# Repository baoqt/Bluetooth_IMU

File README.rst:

================= =====
Supported Targets ESP32
================= =====

BT_IMU_2_0
======================

Firmware and PCB design of an IMU sensor board to be used with stroke rehabilitation and data collection.

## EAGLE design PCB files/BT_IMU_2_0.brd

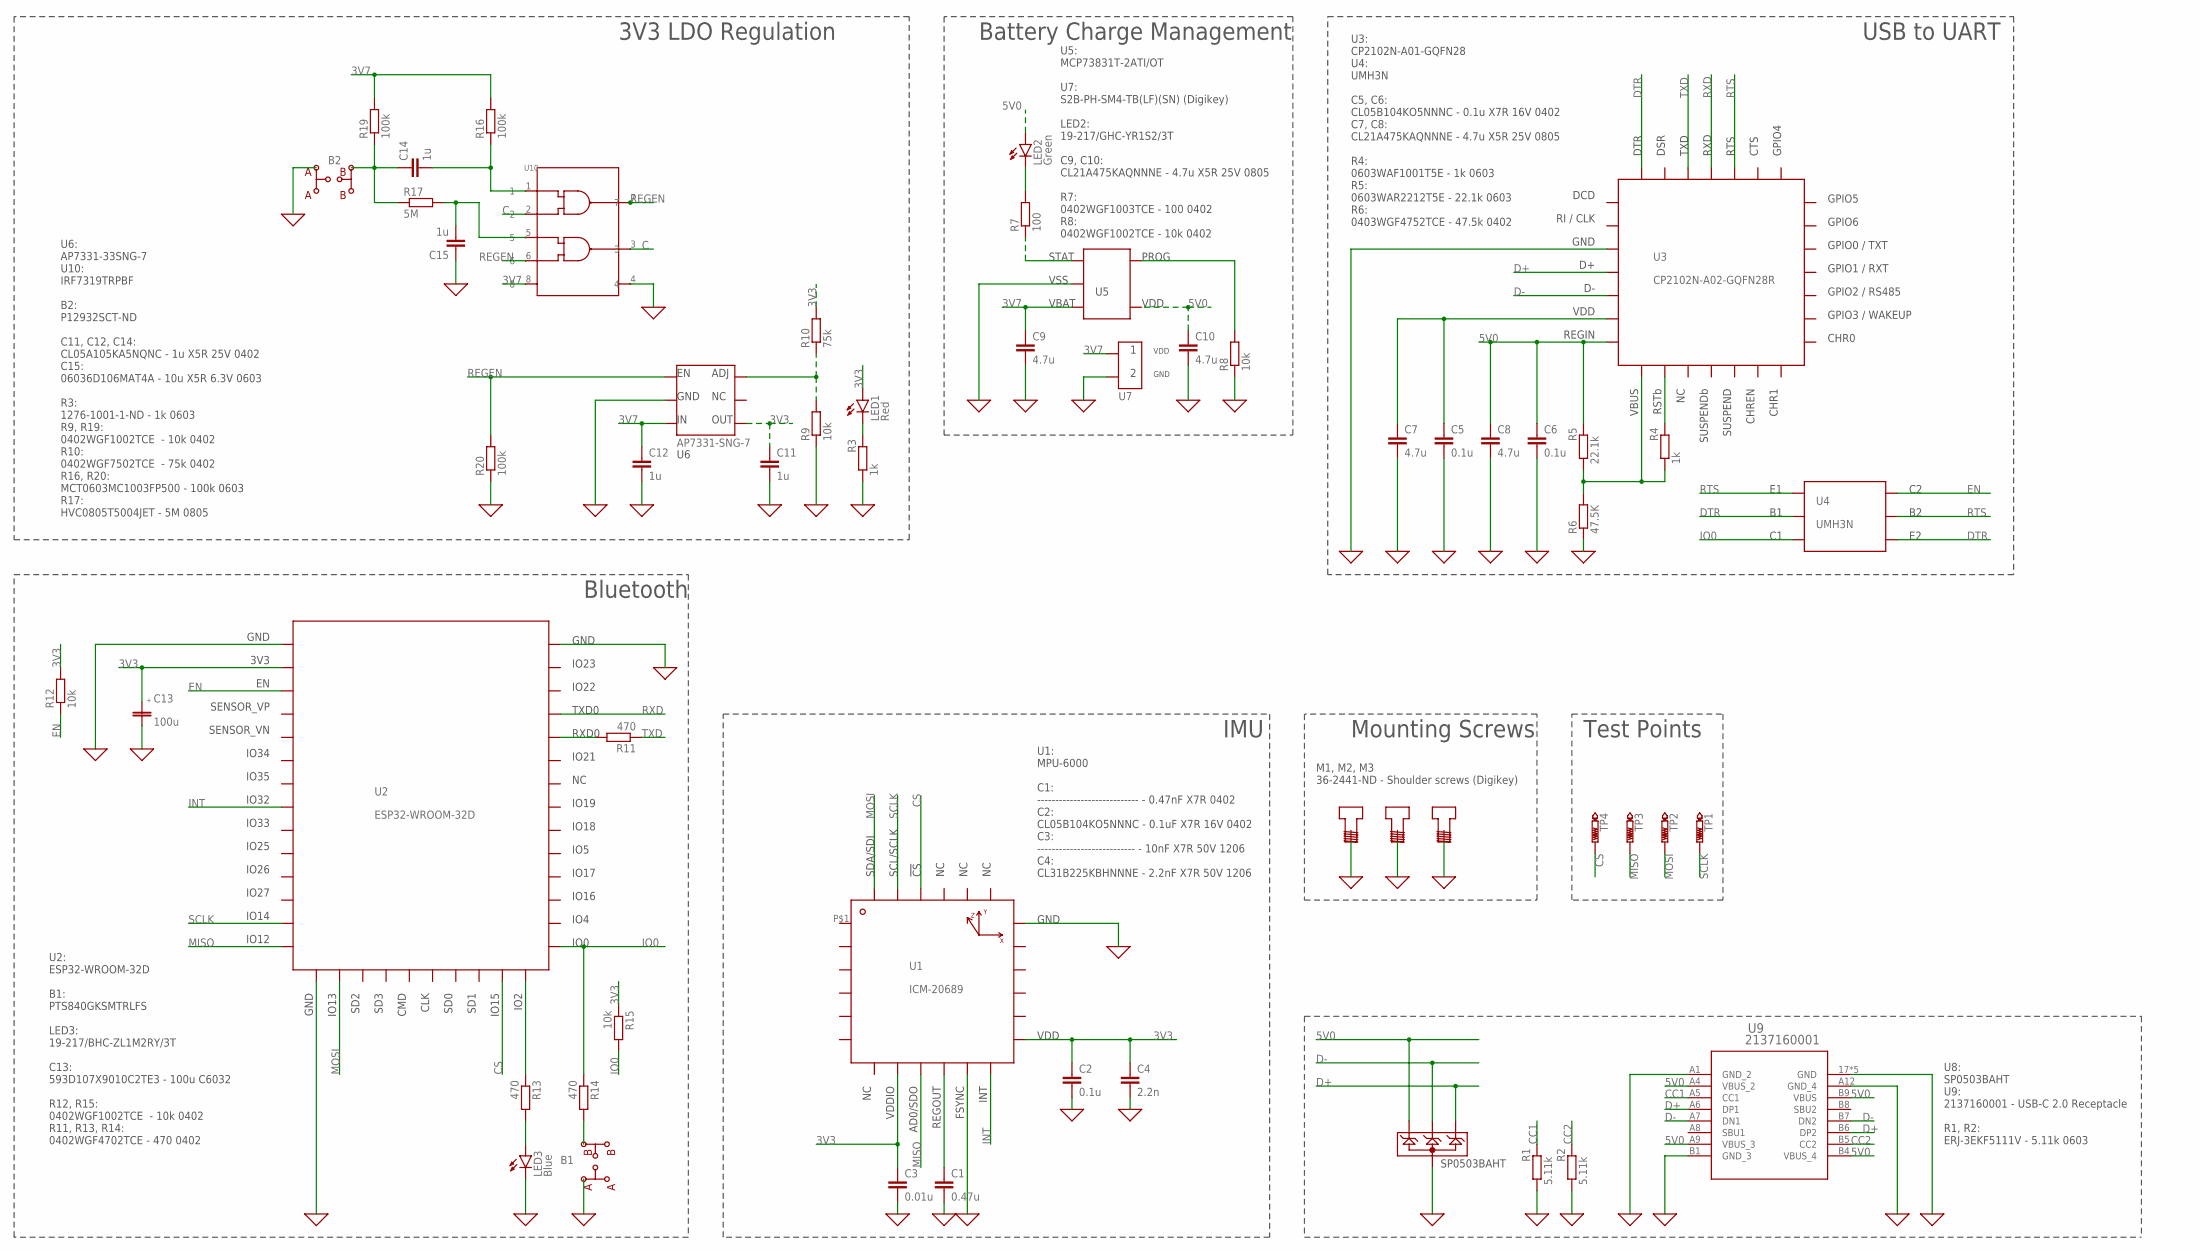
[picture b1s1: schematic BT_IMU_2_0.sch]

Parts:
B1, B2: P12932SCT-ND
C1: 0.47u; C0603
C2, C5, C6: 0.1u; C0402
C3: 0.01u; C0402
C4: 2.2n; C1206
C7, C8, C9, C10: 4.7u; C0805
C11, C12, C14: 1u; C0402
C13: 100u; C6032
C15: 1u; C0603
LED1: Red; CHIP-LED0603
LED2: Green; SML0603
LED3: Blue; SML0603
M1, M2, M3: 2441
R1, R2: 5.11k; R0603
R3, R4: 1k; R0603
R5: 22.1k; R0603
R6: 47.5K; R0402
R7: 100; R0402
R8, R9, R12, R15: 10k; R0402
R10: 75k; R0402
R11, R13, R14: 470; R0402
R16, R19, R20: 100k; R0603
R17: 5M; R0805
TP1, TP2, TP3, TP4: PTR1B1,27; B1,27
U1: ICM-20689; 24-QFN(4X4)
U2: ESP32-WROOM-32D
U3: CP2102N-A02-GQFN28R; 28-QFN(5X5)
U4: UMH3N; UMT6
U5: MCP73831T-2ATI/OT; SOT-23-5
U6: AP7331-SNG-7; U-DFN2020-6
U7: S2B-PH-SM4-TB(LF)(SN)
U8: SP0503BAHT; SOT-143-4
U9: 2137160001; 2137160001_MOL
U10: TC7WZ00FKSOT-765; SOT-765

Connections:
0: B1.P$2, B2.P$2, C1.2, C2.2, C3.2, C4.2, C5.2, C6.2, C7.2, C8.2, C9.2, C10.2, C11.2, C12.2, C13.P$2, C15.1, LED3.C, M1.P$1, M2.P$1, M3.P$1, R1.1, R2.1, R3.1, R6.1, R8.1, R9.1, R20.1, U1.P$11, U1.P$18, U2.P$1, U2.P$15, U2.P$38, U2.P$39, U2.P$40, U2.P$41, U2.P$42, U2.P$43, U2.P$44, U2.P$45, U2.P$46, U2.P$47, U3.P$2, U3.P$28, U3.P$29, U3.P$30, U3.P$31, U3.P$32, U3.P$33, U3.P$34, U3.P$35, U3.P$36, U5.P$2, U6.P$2, U6.P$7, U6.P$8, U7.P$2, U8.P$1, U9.17 (GND), U9.18 (GND), U9.19 (GND), U9.20 (GND), U9.A1 (GND_2), U9.A12 (GND_4), U9.B1 (GND_3), U9.B12 (GND), U10.4
3V3: C2.1, C3.1, C4.1, C11.1, C13.P$1, LED1.A, R10.2, R12.2, R15.1, U1.P$8, U1.P$13, U2.P$2, U6.P$4
3V7: C9.1, C12.1, R16.2, R19.2, U5.P$3, U6.P$3, U7.P$1, U10.8
5V0: C6.1, C8.1, C10.1, LED2.A, R5.2, U3.P$6, U5.P$4, U8.P$2, U9.A4 (VBUS_2), U9.A9 (VBUS_3), U9.B4 (VBUS_4), U9.B9 (VBUS)
C: U10.2, U10.3
CC1: R1.2, U9.A5 (CC1)
CC2: R2.2, U9.B5 (CC2)
CS: TP4.TP, U1.P$22, U2.P$23
D+: U3.P$3, U8.P$4, U9.A6 (DP1), U9.B6 (DP2)
D-: U3.P$4, U8.P$3, U9.A7 (DN1), U9.B7 (DN2)
DTR: U3.P$27, U4.P$2, U4.P$4
EN: R12.1, U2.P$3, U4.P$6
INT: U1.P$12, U2.P$8
IO0: R14.1, R15.2, U2.P$25, U4.P$3
MISO: TP3.TP, U1.P$9, U2.P$14
MOSI: TP2.TP, U1.P$24, U2.P$16
unnamed: C1.1, U1.P$10
unnamed: B1.P$4, R14.2
unnamed: LED1.C, R3.2
unnamed: R4.2, U3.P$8
unnamed: R4.1, R5.1, R6.2, U3.P$7
unnamed: C5.1, C7.1, U3.P$5
unnamed: R7.1, U5.P$1
unnamed: R11.2, U2.P$34
unnamed: R8.2, U5.P$5
unnamed: LED2.C, R7.2
unnamed: R9.2, R10.1, U6.P$6
unnamed: R13.1, U2.P$24
unnamed: C15.2, R17.2, U10.5
unnamed: B2.P$4, C14.1, R17.1, R19.1
unnamed: LED3.A, R13.2
unnamed: C14.2, R16.1, U10.1
REGEN: R20.2, U6.P$1, U10.6, U10.7
RTS: U3.P$23, U4.P$1, U4.P$5
RXD: U2.P$35, U3.P$24
SCLK: TP1.TP, U1.P$23, U2.P$13
TXD: R11.1, U3.P$25

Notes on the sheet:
U1: MPU-6000 C1: ---------------------------- - 0.47nF X7R 0402 C2: CL05B104KO5NNNC - 0.1uF X7R 16V 0402 C3: --------------------------- - 10nF X7R 50V 1206 C4: CL31B225KBHNNNE - 2.2nF X7R 50V 1206
U3: CP2102N-A01-GQFN28 U4: UMH3N C5, C6: CL05B104KO5NNNC - 0.1u X7R 16V 0402 C7, C8: CL21A475KAQNNNE - 4.7u X5R 25V 0805 R4: 0603WAF1001T5E - 1k 0603 R5: 0603WAR2212T5E - 22.1k 0603 R6: 0403WGF4752TCE - 47.5k 0402
USB to UART
IMU
M1, M2, M3 36-2441-ND - Shoulder screws (Digikey)
U5: MCP73831T-2ATI/OT U7: S2B-PH-SM4-TB(LF)(SN) (Digikey) LED2: 19-217/GHC-YR1S2/3T C9, C10: CL21A475KAQNNNE - 4.7u X5R 25V 0805 R7: 0402WGF1003TCE - 100 0402 R8: 0402WGF1002TCE - 10k 0402
U6: AP7331-33SNG-7 U10: IRF7319TRPBF B2: P12932SCT-ND C11, C12, C14: CL05A105KA5NQNC - 1u X5R 25V 0402 C15: 06036D106MAT4A - 10u X5R 6.3V 0603 R3: 1276-1001-1-ND - 1k 0603 R9, R19: 0402WGF1002TCE - 10k 0402 R10: 0402WGF7502TCE - 75k 0402 R16, R20: MCT0603MC1003FP500 - 100k 0603 R17: HVC0805T5004JET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
Battery Charge Management
Mounting Screws
3V3 LDO Regulation
Bluetooth
U2: ESP32-WROOM-32D B1: PTS840GKSMTRLFS LED3: 19-217/BHC-ZL1M2RY/3T C13: 593D107X9010C2TE3 - 100u C6032 R12, R15: 0402WGF1002TCE - 10k 0402 R11, R13, R14: 0402WGF4702TCE - 470 0402
Test Points
U8: SP0503BAHT U9: 2137160001 - USB-C 2.0 Receptacle R1, R2: ERJ-3EKF5111V - 5.11k 0603

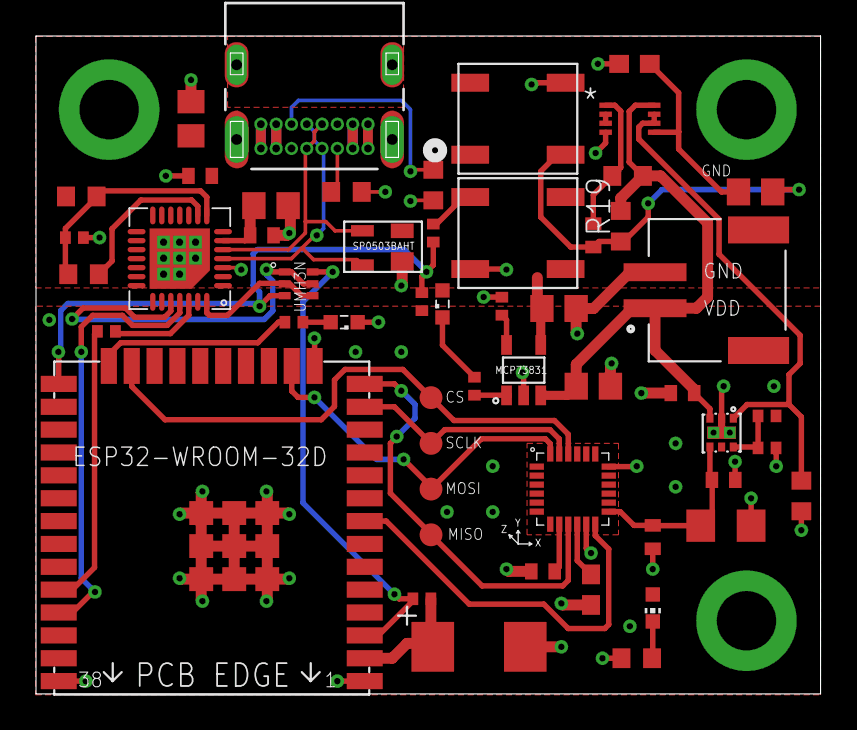
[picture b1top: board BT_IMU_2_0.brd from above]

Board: 4 copper layers, 43.6 x 36.5 mm, 58 parts (0 on the bottom side), 37 nets.

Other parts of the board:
U$1: SIGNATURE
U$2: TENA_LOGO

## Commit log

2021-01-06 Recreated project on newer esp-idf version. Made changes to the FIFO, now works correctly.
2021-01-17 Adjusted output multipliers. Accelerometer output now in m/s^2 instead of Gs.
2021-01-17 Added build changes.
2021-02-13 Modified polling rate and noise bandwidth of accelerometer.
2021-05-30 Fixed sampling rate
2021-05-31 Added sensor's internal FIFO functionality. Reduced Bluetooth forwarding frequency from 10Hz to 3Hz.
2021-10-09 Minor adjustments to code.
2021-10-09 Added PCB files folder containing EAGLE project files.
2021-10-16 Fix issue with scaling.
2022-02-19 Update to filtering.
2022-04-04 Adjusted message format of data points
    Removed leading comma originally used for timestamps
    Removed spaces after each comma to save on data usage of each file
2022-04-25 Removed calibration step

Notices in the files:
parts and their libraries:
COPYRIGHT: Copyright (C) 2018 Accelerated Designs. All rights reserved
Toshiba: COPYRIGHT: Copyright (C) 2021 Ultra Librarian. All rights reserved.
